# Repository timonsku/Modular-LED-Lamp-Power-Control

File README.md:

# Modular-LED-Lamp-Power-Control
For more details see https://hackaday.io/project/20653-dirt-cheap-modular-led-lighting-system

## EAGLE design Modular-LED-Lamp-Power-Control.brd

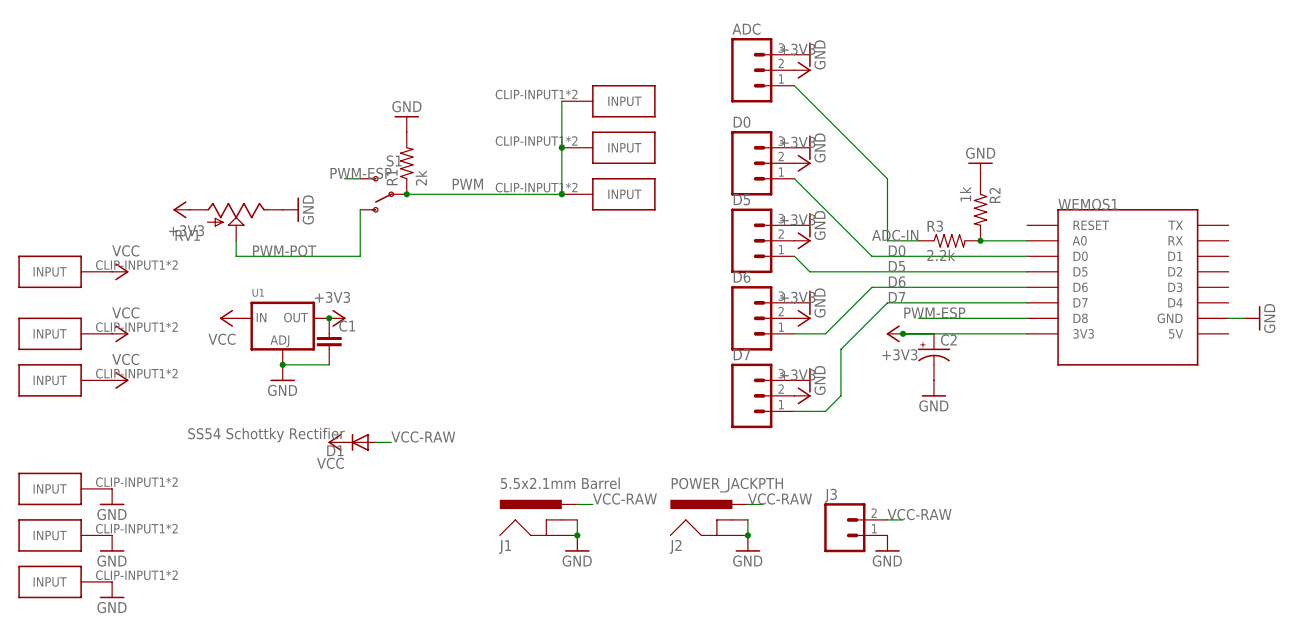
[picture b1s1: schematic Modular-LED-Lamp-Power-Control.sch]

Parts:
ADC: M03PTH; 1X03
C1: CAP1206; 1206
C2: CAP_POLE; PANASONIC_E
D0, D5, D6, D7: M03PTH; 1X03
D1: SS54 Schottky Rectifier; DO214AB
GND-CLIP, GND-CLIP1, GND-CLIP2: GND; FUSE-HOLDER-5X20MM
J1: 5.5x2.1mm Barrel; POWER_JACK_SMD
J2: POWER_JACKPTH; POWER_JACK_PTH
J3: M025MM; SCREWTERMINAL-5MM-2
PWM-CLIP, PWM-CLIP1, PWM-CLIP2: FUSE-HOLDER-5X20MM
R1: 2k; 1206
R2: 1k; 1206
R3: 2.2k; 1206
RV1: POT-RV16AF-20; POT_ALPHA_RV16AF-20
S1: SWITCH-SPDTPTH; SWITCH-SPDT
U1: LM1117SOT223-WAVE; SOT223-W
VCC-CLIP, VCC-CLIP1, VCC-CLIP2: FUSE-HOLDER-5X20MM
WEMOS1: WEMOS-D1-MINI

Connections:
+3V3: ADC.2, C1.1, C2.+, D0.2, D5.2, D6.2, D7.2, RV1.1 (A), U1.2 (OUT), WEMOS1.3V3
A0: R2.2, R3.2, WEMOS1.A0
ADC-IN: ADC.1, R3.1
D0: D0.1, WEMOS1.D0
D5: D5.1, WEMOS1.D5
D6: D6.1, WEMOS1.D6
D7: D7.1, WEMOS1.D7
GND: ADC.3, C1.2, C2.-, D0.3, D5.3, D6.3, D7.3, GND-CLIP.CLIP-INPUT1, GND-CLIP.CLIP-INPUT2, GND-CLIP1.CLIP-INPUT1, GND-CLIP1.CLIP-INPUT2, GND-CLIP2.CLIP-INPUT1, GND-CLIP2.CLIP-INPUT2, J1.GND (GNDBREAK), J1.P$4 (GND), J2.GND, J2.GNDBREAK, J3.1, R1.2, R2.1, RV1.3 (E), U1.1 (ADJ), WEMOS1.GND
PWM: PWM-CLIP.CLIP-INPUT1, PWM-CLIP.CLIP-INPUT2, PWM-CLIP1.CLIP-INPUT1, PWM-CLIP1.CLIP-INPUT2, PWM-CLIP2.CLIP-INPUT1, PWM-CLIP2.CLIP-INPUT2, R1.1, S1.2
PWM-ESP: S1.3 (S), WEMOS1.D8
PWM-POT: RV1.2 (S), S1.1 (O)
VCC: D1.C, U1.3 (IN), VCC-CLIP.CLIP-INPUT1, VCC-CLIP.CLIP-INPUT2, VCC-CLIP1.CLIP-INPUT1, VCC-CLIP1.CLIP-INPUT2, VCC-CLIP2.CLIP-INPUT1, VCC-CLIP2.CLIP-INPUT2
VCC-RAW: D1.A, J1.VIN0 (PWR), J2.PWR, J3.2

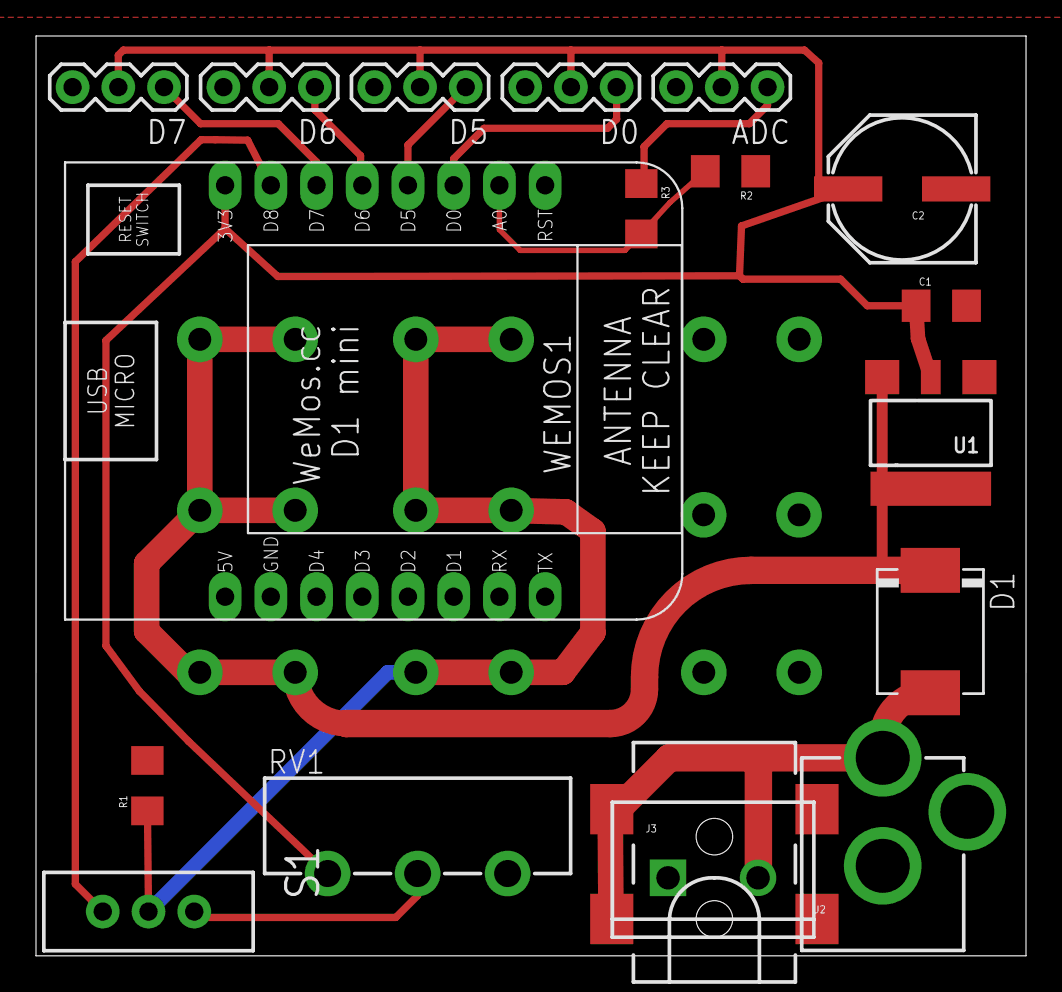
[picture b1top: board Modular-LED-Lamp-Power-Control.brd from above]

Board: 2 copper layers, 55.0 x 51.1 mm, 27 parts (0 on the bottom side), 13 nets.

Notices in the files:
parts and their libraries:
SparkFun-Electromechanical: Licensing: Creative Commons ShareAlike 4.0 International - https://creativecommons.org/licenses/by-sa/4.0
microbuilder: This work is placed in the public domain, and may be freely used for commercial and non-commercial work with the following conditions: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
